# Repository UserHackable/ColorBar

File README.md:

## LED Color Bar

This is intended to be used to light up a glass sculpture or etching on glass or plexiglass. 

The usb level shifting components would theoretically allow you to control the colors over the USB port, but I haven't goten around to trying that yet. 

The small oval LED's are CREE 4mm ovals 
## ColorBar 

### Board dimensions

* (290000, 90000) original units
* (2.9000, 0.9000) inches
* (73.6600, 22.8600) mm

| Front | Back |
| --- | --- |
|  |  |

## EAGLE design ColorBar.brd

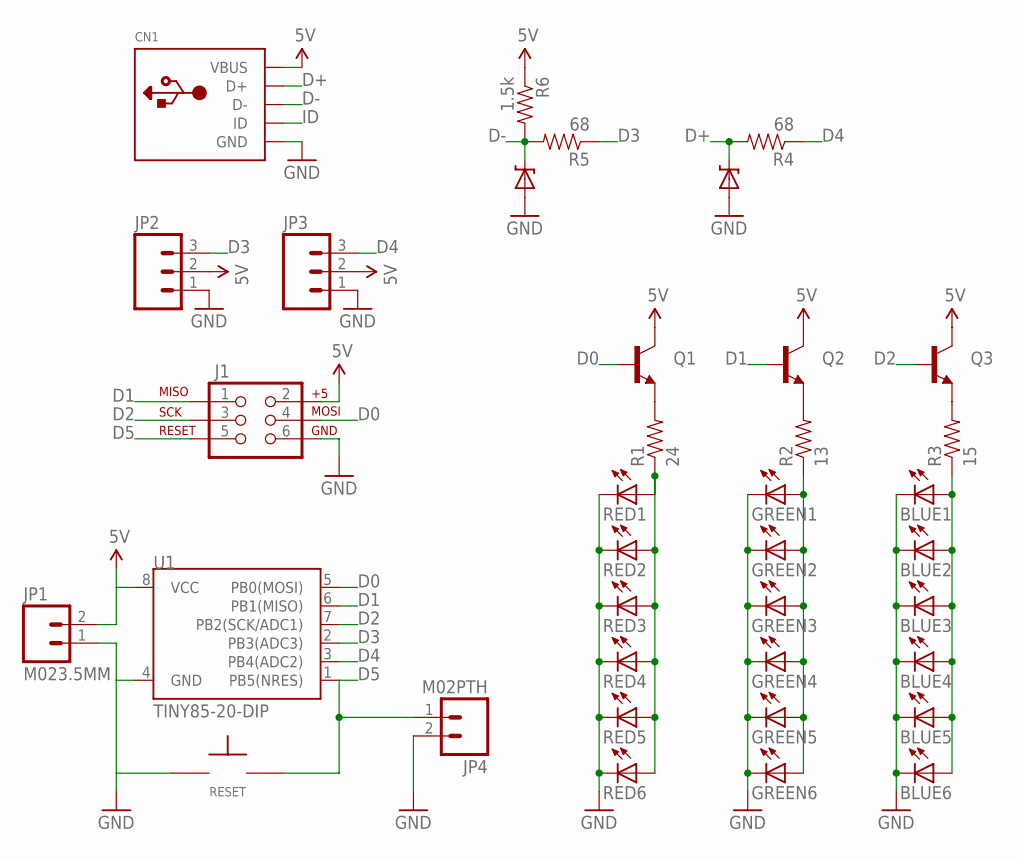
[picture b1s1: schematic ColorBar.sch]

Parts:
BLUE1, BLUE2, BLUE3, BLUE4, BLUE5, BLUE6: LEDOVAL; LED-OVAL
CN1: USBMOLEX; USB-MINIB-THM-MOLEX
GREEN1, GREEN2, GREEN3, GREEN4, GREEN5, GREEN6: LEDOVAL; LED-OVAL
J1: AVR_SPI_PRG_6LABELED; 2X3-NS
JP1: M023.5MM; SCREWTERMINAL-3.5MM-2
JP2, JP3: M03PTH; 1X03
JP4: M02PTH; 1X02
Q1, Q2, Q3: TRANSISTOR_NPNTO-92-AMMO; TO-92-AMMO
R1: 24; AXIAL-0.3
R2: 13; AXIAL-0.3
R3: 15; AXIAL-0.3
R4, R5: 68; AXIAL-0.3
R6: 1.5k; AXIAL-0.3
RED1, RED2, RED3, RED4, RED5, RED6: LEDOVAL; LED-OVAL
RESET: TAC_SPST_NO
U1: TINY85-20-DIP; DIP08
U$1, U$2: 3.6; DIODE-ZENER

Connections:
5V: CN1.VBUS, J1.2 (V+), JP1.2, JP2.2, JP3.2, Q1.3 (C), Q2.3 (C), Q3.3 (C), R6.P$1 (1), U1.8 (VCC)
BLUE: BLUE1.ANODE (A), BLUE2.ANODE (A), BLUE3.ANODE (A), BLUE4.ANODE (A), BLUE5.ANODE (A), BLUE6.ANODE (A), R3.P$1 (1)
D0: J1.4 (MOSI), Q1.2 (B), U1.5 (PB0(MOSI))
D1: J1.1 (MISO), Q2.2 (B), U1.6 (PB1(MISO))
D2: J1.3 (SCK), Q3.2 (B), U1.7 (PB2(SCK/ADC1))
D3: JP2.3, R5.P$1 (1), U1.2 (PB3(ADC3))
D4: JP3.3, R4.P$1 (1), U1.3 (PB4(ADC2))
D5: J1.5 (RST), JP4.1, RESET.P$2, U1.1 (PB5(NRES))
D+: CN1.D+, R4.P$2 (2), U$2.P$1 (C)
D-: CN1.D-, R5.P$2 (2), R6.P$2 (2), U$1.P$1 (C)
GND: BLUE1.CATHODE (C), BLUE2.CATHODE (C), BLUE3.CATHODE (C), BLUE4.CATHODE (C), BLUE5.CATHODE (C), BLUE6.CATHODE (C), CN1.GND, GREEN1.CATHODE (C), GREEN2.CATHODE (C), GREEN3.CATHODE (C), GREEN4.CATHODE (C), GREEN5.CATHODE (C), GREEN6.CATHODE (C), J1.6 (GND), JP1.1, JP2.1, JP3.1, JP4.2, RED1.CATHODE (C), RED2.CATHODE (C), RED3.CATHODE (C), RED4.CATHODE (C), RED5.CATHODE (C), RED6.CATHODE (C), RESET.P$1, U1.4 (GND), U$1.P$2 (A), U$2.P$2 (A)
GREEN: GREEN1.ANODE (A), GREEN2.ANODE (A), GREEN3.ANODE (A), GREEN4.ANODE (A), GREEN5.ANODE (A), GREEN6.ANODE (A), R2.P$1 (1)
ID: CN1.ID
unnamed: Q1.1 (E), R1.P$2 (2)
unnamed: Q2.1 (E), R2.P$2 (2)
unnamed: Q3.1 (E), R3.P$2 (2)
RED: R1.P$1 (1), RED1.ANODE (A), RED2.ANODE (A), RED3.ANODE (A), RED4.ANODE (A), RED5.ANODE (A), RED6.ANODE (A)

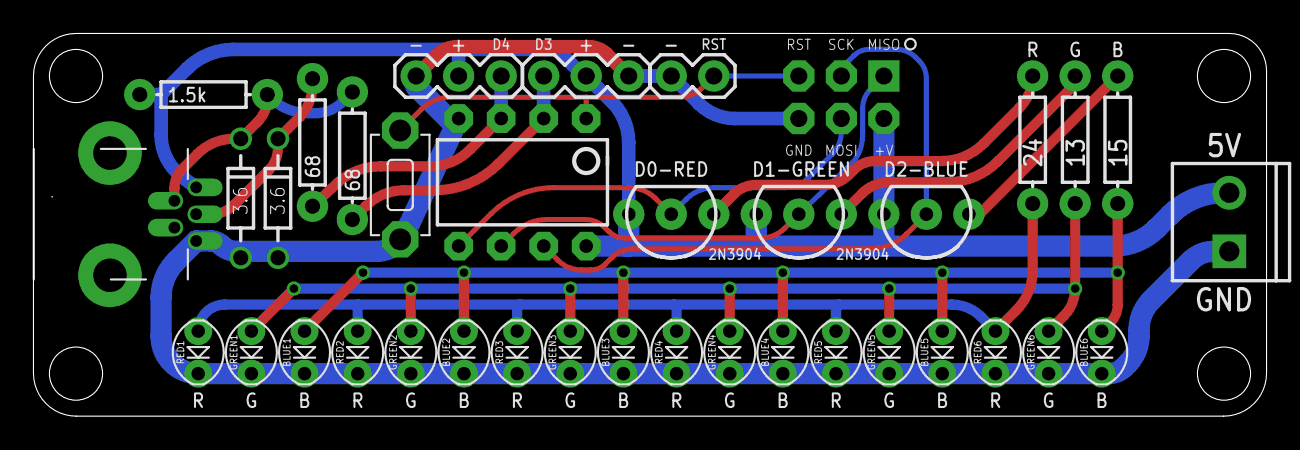
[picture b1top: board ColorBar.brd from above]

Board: 2 copper layers, 73.7 x 22.9 mm, 37 parts (0 on the bottom side), 16 nets.

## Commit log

2016-04-08 from Makefile

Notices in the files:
parts and their libraries:
SparkFun-DigitalIC: Licensing: Creative Commons ShareAlike 4.0 International - https://creativecommons.org/licenses/by-sa/4.0
